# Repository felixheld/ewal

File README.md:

# ewal

The electric water level is a small project which uses a 3-axis accelerometer, a microcontroller (ATTiny48) and 5 LEDs to act as a digital water level.

It is used as a small project to teach people SMD soldering with stencils, solder paste and a soldering oven.

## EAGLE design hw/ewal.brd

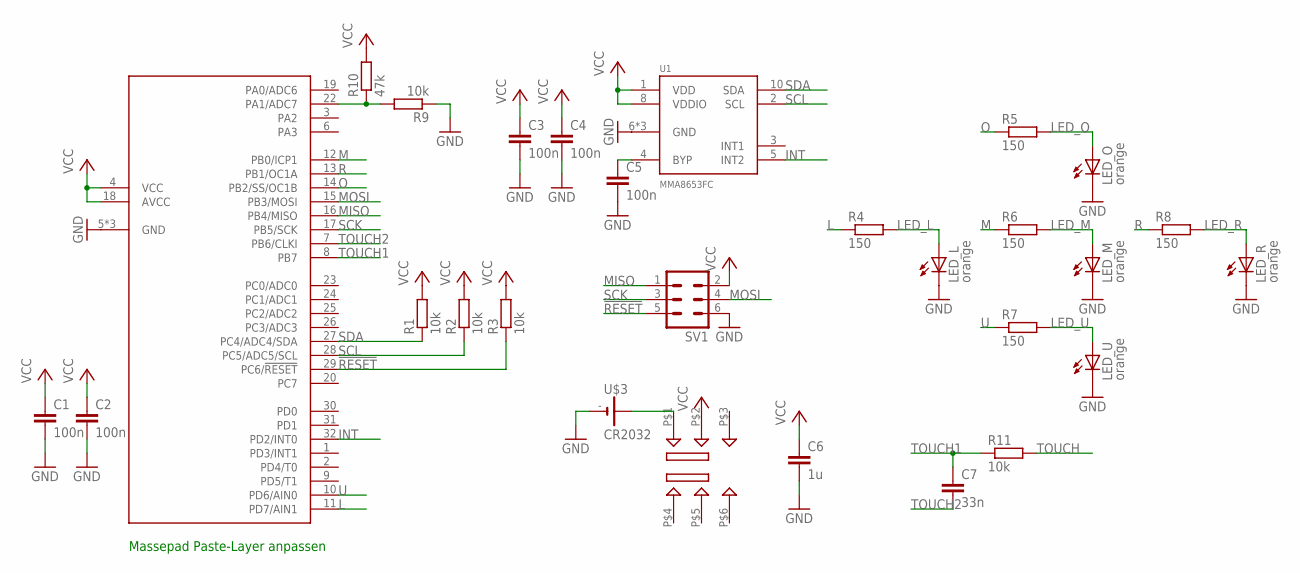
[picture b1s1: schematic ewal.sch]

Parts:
C1, C2, C3, C4, C5: 100n; C0603
C6: 1u; C0805
C7: 33n; C0603
LED_L: orange; CHIP-LED0603
LED_M: orange; CHIP-LED0603
LED_O: orange; CHIP-LED0603
LED_R: orange; CHIP-LED0603
LED_U: orange; CHIP-LED0603
R1, R2, R3, R9, R11: 10k; R0603
R4, R5, R6, R7, R8: 150; R0603
R10: 47k; R0603
SV1: MA03-2
U1: MMA8653FC; 2X2_DFN_LONGPADS
U2: ATTINY48; MLF32-TH
U$3: CR2032; BK-912
U$4: JS202011SCQN

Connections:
!RESET: R3.1, SV1.5, U2.29 (PC6/!RESET)
GND: C1.2, C2.2, C3.2, C4.2, C5.2, C6.2, LED_L.C, LED_M.C, LED_O.C, LED_R.C, LED_U.C, R9.1, SV1.6, U1.6 (GND), U1.7 (GND), U1.9 (GND), U2.5 (GND), U2.21 (GND), U2.TH (GND), U$3.-
INT: U1.5 (INT2), U2.32 (PD2/INT0)
L: R4.1, U2.11 (PD7/AIN1)
LED_L: LED_L.A, R4.2
LED_M: LED_M.A, R6.2
LED_O: LED_O.A, R5.2
LED_R: LED_R.A, R8.2
LED_U: LED_U.A, R7.2
M: R6.1, U2.12 (PB0/ICP1)
MISO: SV1.1, U2.16 (PB4/MISO)
MOSI: SV1.4, U2.15 (PB3/MOSI)
unnamed: C5.1, U1.4 (BYP)
O: R5.1, U2.14 (PB2/SS/OC1B)
R: R8.1, U2.13 (PB1/OC1A)
SCK: SV1.3, U2.17 (PB5/SCK)
SCL: R2.1, U1.2 (SCL), U2.28 (PC5/ADC5/SCL)
SDA: R1.1, U1.10 (SDA), U2.27 (PC4/ADC4/SDA)
TOUCH: R11.2
TOUCH1: C7.1, R11.1, U2.8 (PB7)
TOUCH2: C7.2, U2.7 (PB6/CLKI)
U: R7.1, U2.10 (PD6/AIN0)
VCC: C1.1, C2.1, C3.1, C4.1, C6.1, R1.2, R2.2, R3.2, R10.2, SV1.2, U1.1 (VDD), U1.8 (VDDIO), U2.4 (VCC), U2.18 (AVCC), U$4.P$2
V_BAT: U$3.+@1 (+), U$3.+@2 (+), U$4.P$1
V_SENSE: R9.2, R10.1, U2.22 (PA1/ADC7)

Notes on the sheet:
Massepad Paste-Layer anpassen

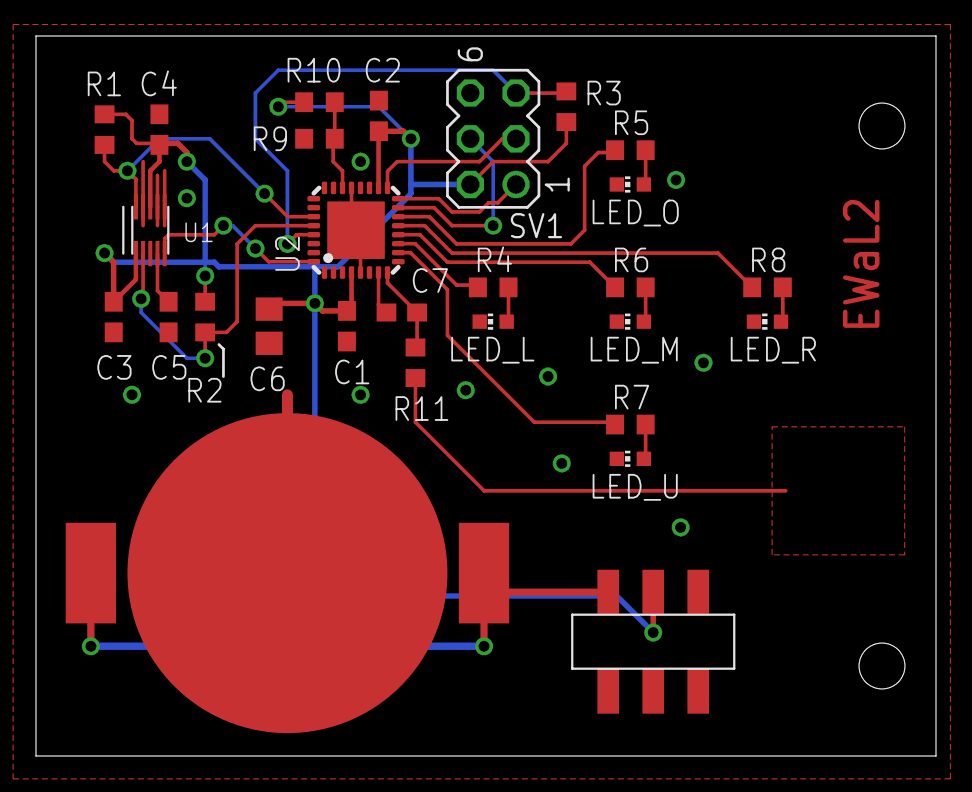
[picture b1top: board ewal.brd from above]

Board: 2 copper layers, 50.0 x 40.0 mm, 28 parts (0 on the bottom side), 24 nets.

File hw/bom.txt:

Stückliste exportiert aus /Users/felix/ewal/hw/ewal.sch am 11.11.14 00:35

Qty Value        Device          Package          Parts
1                MA03-2          MA03-2           SV1                               (nicht bestückt)
5   100n         C-EUC0603       C0603            C1, C2, C3, C4, C5
5   10k          R-EU_R0603      R0603            R1, R2, R3, R9, R11
5   150          R-EU_R0603      R0603            R4, R5, R6, R7, R8
1   1u           C-EUC0805       C0805            C6
1   33n          C-EUC0603       C0603            C7
1   47k          R-EU_R0603      R0603            R10
1   ATTINY48     ATTINY48        MLF32-TH         U2
1   CR2032       CR2032          BK-912           U$3
1   JS202011SCQN JS202011SCQN    JS202011SCQN     U$4
1   MMA8653FC    MMA8653FC       2X2_DFN_LONGPADS U1
5   orange       LEDCHIP-LED0603 CHIP-LED0603     LED_L, LED_M, LED_O, LED_R, LED_U LED

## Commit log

2014-01-26 create schematic and layout of hardware
2014-04-21 add bill of materials
2014-04-23 remove silkscreen from the accelerometer's pads
2014-06-21 initial software release on the GPN14
    the electronic water bubble function is only implemented for one orientation
    Peter Fleury's TWI library is used for i2c communication
2014-11-09 update to version 2
    now with a touch sensor and a different stencil layout for the sensor
2014-11-10 update the bill of materials
2014-11-24 Set solder paste reduction to 20%
2014-11-24 add component library
2014-11-25 Fixed thermal pad paste aperture, was too big previously
2014-11-26 Added filtering and different orientation cases, aswell as a Makefile
2014-11-26 Modified .gitignore to ignore gerber output files
2014-11-26 add avrdude config file with attiny48 support
2014-11-27 Fixed minor errors in Wall-mode and filtering
2014-11-27 misc
2014-11-27 Added PWM for LEDs
2014-11-29 Add Calibration defines and a deadzone for the PWM
2014-12-25 add assembling instructions
2014-12-25 move and update assembly instructions
2014-12-25 update software release binary
